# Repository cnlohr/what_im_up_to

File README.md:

# what_im_up_to
Charles: Stop putting things here, and put them in TODO.

99C99in99
 * Thinking Procedurally
 * main(...) and functions.
 * variables
 * 
 * /proc/cmdline
 * /proc/mem
 * /proc/maps

Interesting C:
 * /proc/cmdline
 * /proc/maps, /proc/exe, objdump
 
Other videos:
 * Engineering, getting from here to there.
 * James 3:3 When we put bits into the mouths of horses to make them obey us, we can turn the whole animal. 4 Or take ships as an example. Although they are so large and are driven by strong winds, they are steered by a very small rudder wherever the pilot wants to go

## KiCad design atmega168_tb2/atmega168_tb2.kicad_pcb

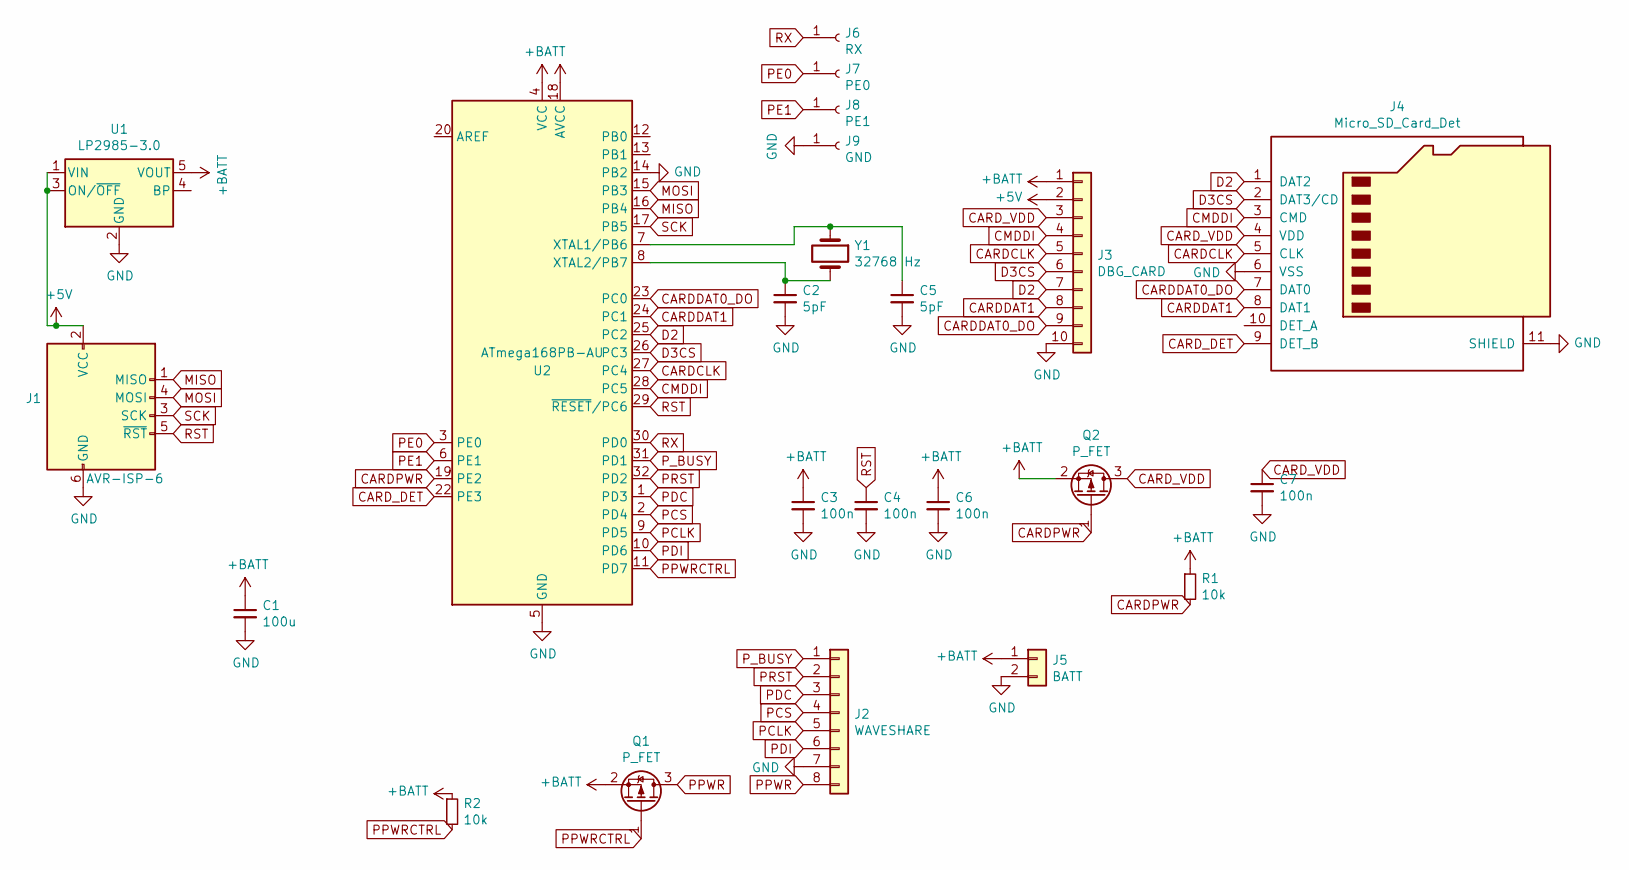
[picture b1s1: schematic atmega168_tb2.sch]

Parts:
C1: 100u; C_1206_3216Metric
C2, C5: 5pF; C_0603_1608Metric
C3, C4, C6, C7: 100n; C_0603_1608Metric
J1: AVR-ISP-6; PinHeader_2x03_P2.54mm_Vertical_SMD
J2: WAVESHARE; PinHeader_1x08_P2.54mm_Vertical_SMD_Pin1Left
J3: DBG_CARD; PinHeader_1x10_P2.54mm_Vertical_SMD_Pin1Right
J4: Micro_SD_Card_Det; MicroSD-HYC77-TF09-200
J5: BATT; PinHeader_1x02_P2.54mm_Vertical_SMD_Pin1Left
J6: RX; TestPoint_Pad_2.5x2.5mm
J7: PE0; TestPoint_Pad_2.5x2.5mm
J8: PE1; TestPoint_Pad_2.5x2.5mm
J9: GND; TestPoint_Pad_2.5x2.5mm
Q1, Q2: P_FET; SOT-23
R1, R2: 10k; R_0603_1608Metric
U1: LP2985-3.0; SOT-23-5
U2: ATmega168PB-AU; TQFP-32_7x7mm_P0.8mm
Y1: 32768 Hz; Crystal_SMD_3215-2Pin_3.2x1.5mm

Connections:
+5V: J1.2 (VCC), J3.2, U1.1 (VIN), U1.3 (ON/~OFF~)
+BATT: C1.1, C3.1, C6.1, J3.1, J5.1, Q1.2 (S), Q2.2 (S), R1.1, R2.1, U1.5 (VOUT), U2.4 (VCC), U2.18 (AVCC)
CARDCLK: J3.5, J4.5 (CLK), U2.27 (PC4)
CARDDAT0_DO: J3.9, J4.7 (DAT0), U2.23 (PC0)
CARDDAT1: J3.8, J4.8 (DAT1), U2.24 (PC1)
CARDPWR: Q2.1 (G), R1.2, U2.19 (PE2)
CARD_DET: J4.9 (DET_B), U2.22 (PE3)
CARD_VDD: C7.1, J3.3, J4.4 (VDD), Q2.3 (D)
CMDDI: J3.4, J4.3 (CMD), U2.28 (PC5)
D2: J3.7, J4.1 (DAT2), U2.25 (PC2)
D3CS: J3.6, J4.2 (DAT3/CD), U2.26 (PC3)
GND: C1.2, C2.2, C3.2, C4.2, C5.2, C6.2, C7.2, J1.6 (GND), J2.7, J3.10, J4.6 (VSS), J4.11 (SHIELD), J5.2, J9.1, U1.2 (GND), U2.5 (GND), U2.14 (PB2), U2.21 (GND)
MISO: J1.1 (MISO), U2.16 (PB4)
MOSI: J1.4 (MOSI), U2.15 (PB3)
unnamed: C2.1, U2.8 (XTAL2/PB7), Y1.2
unnamed: C5.1, U2.7 (XTAL1/PB6), Y1.1
PCLK: J2.5, U2.9 (PD5)
PCS: J2.4, U2.2 (PD4)
PDC: J2.3, U2.1 (PD3)
PDI: J2.6, U2.10 (PD6)
PE0: J7.1, U2.3 (PE0)
PE1: J8.1, U2.6 (PE1)
PPWR: J2.8, Q1.3 (D)
PPWRCTRL: Q1.1 (G), R2.2, U2.11 (PD7)
PRST: J2.2, U2.32 (PD2)
P_BUSY: J2.1, U2.31 (PD1)
RST: C4.1, J1.5 (~RST), U2.29 (~RESET~/PC6)
RX: J6.1, U2.30 (PD0)
SCK: J1.3 (SCK), U2.17 (PB5)

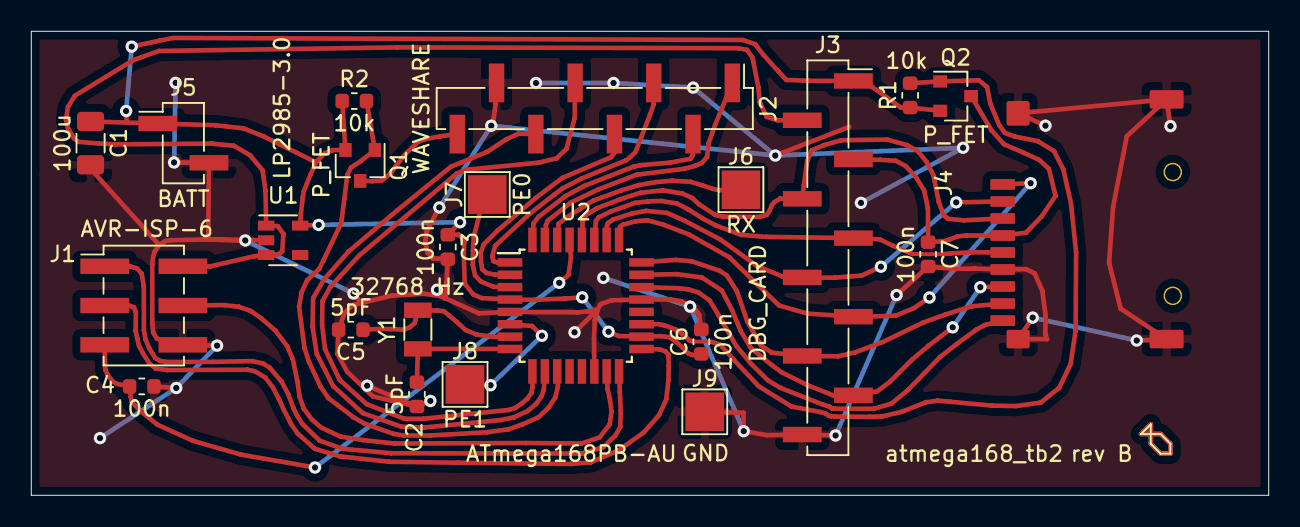
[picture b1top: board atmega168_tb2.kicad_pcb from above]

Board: 2 copper layers, 80.0 x 30.0 mm, 23 parts (0 on the bottom side), 29 nets.

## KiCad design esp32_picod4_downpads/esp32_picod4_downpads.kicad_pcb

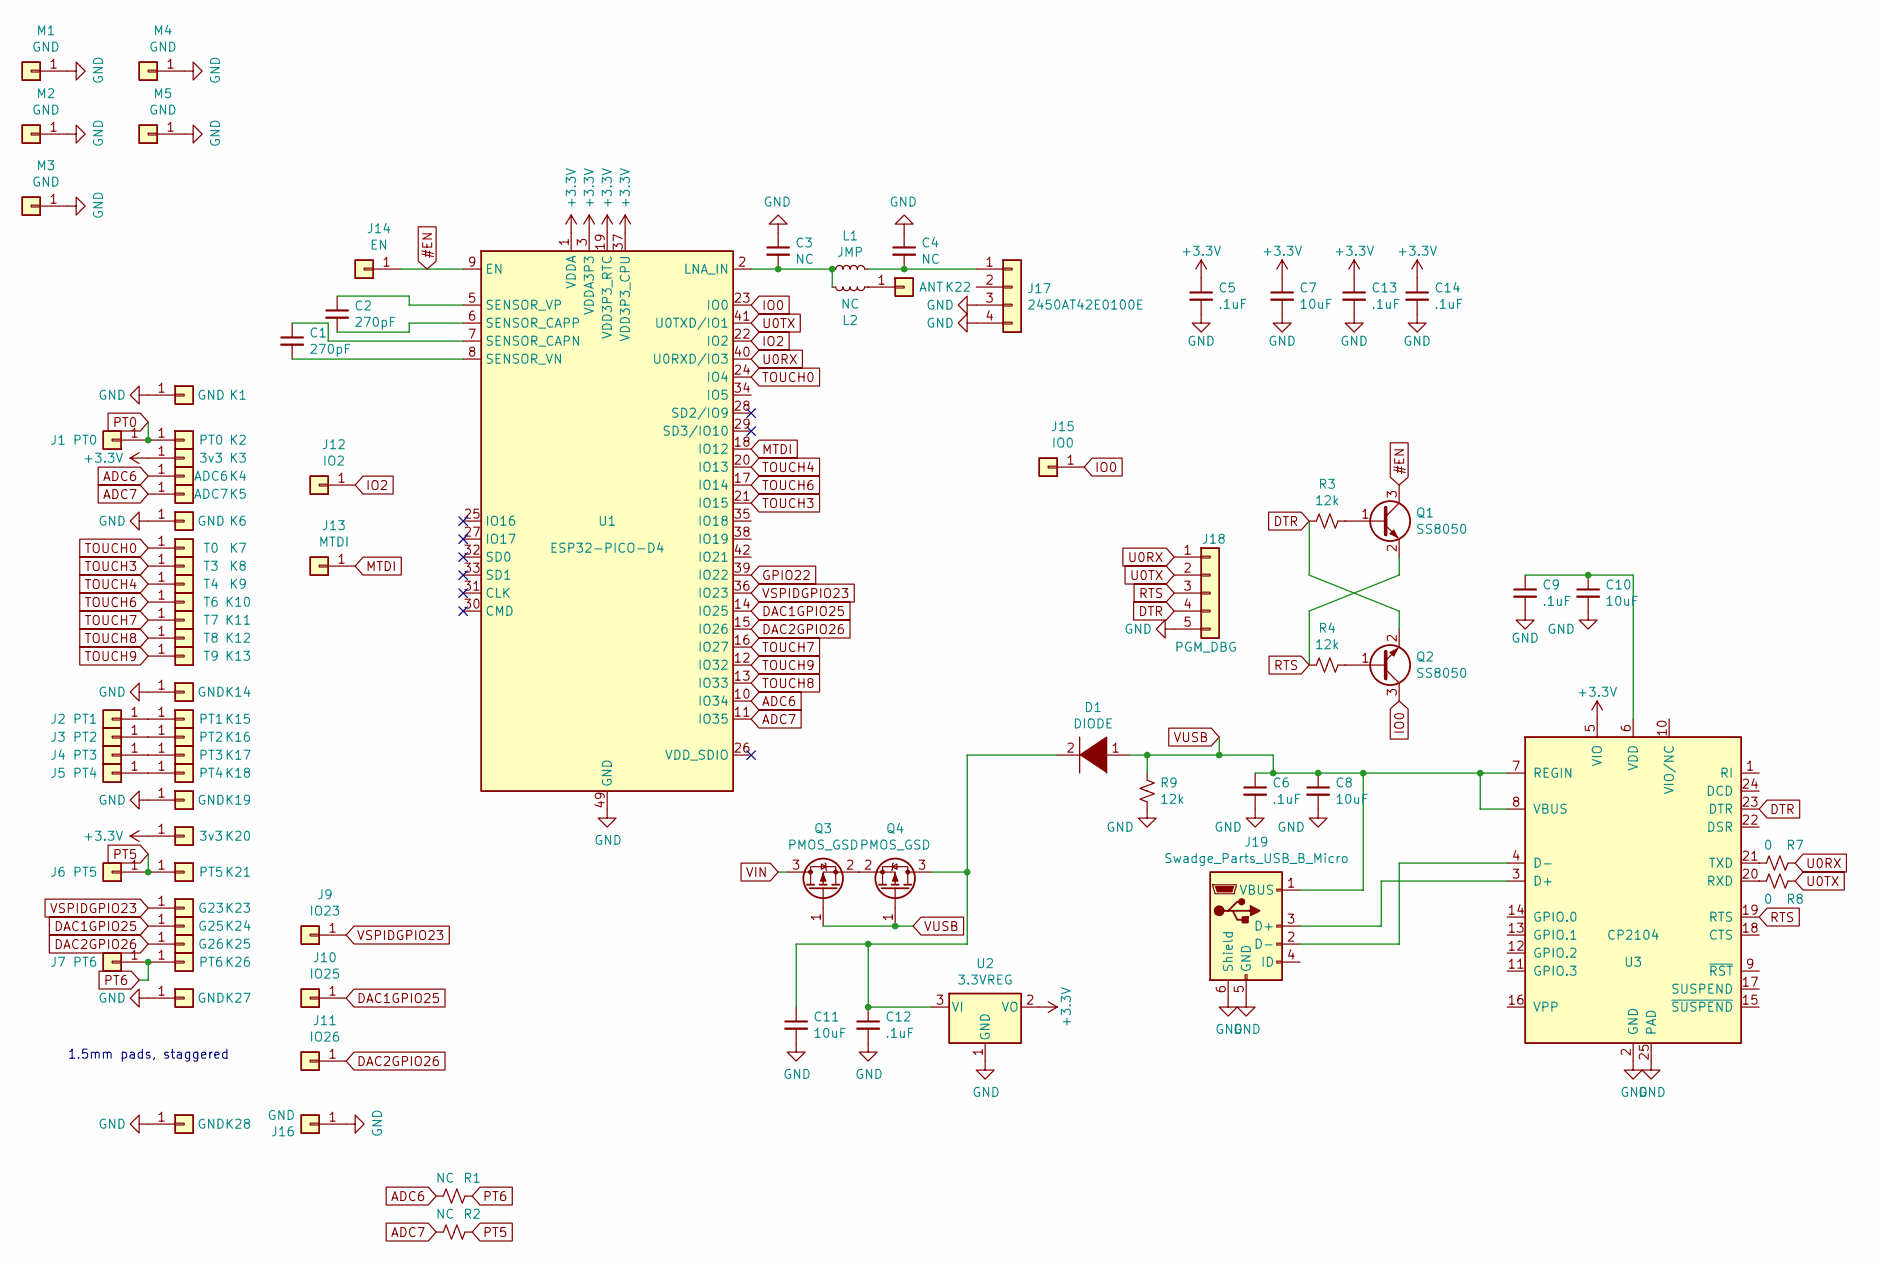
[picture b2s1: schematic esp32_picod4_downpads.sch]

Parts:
C1, C2: 270pF; C_0603_1608Metric
C3, C4: NC; C_0603_1608Metric
C5, C6, C9, C12, C13, C14: .1uF; C_0603_1608Metric
C7, C8, C10, C11: 10uF; C_0603_1608Metric
D1: DIODE; D_SOD-123
J1: PT0; TestPoint_Pad_D1.5mm
J2: PT1; TestPoint_Pad_D1.5mm
J3: PT2; TestPoint_Pad_D1.5mm
J4: PT3; TestPoint_Pad_D1.5mm
J5: PT4; TestPoint_Pad_D1.5mm
J6: PT5; TestPoint_Pad_D1.5mm
J7: PT6; TestPoint_Pad_D1.5mm
J9: IO23; TestPoint_Pad_D1.5mm
J10: IO25; TestPoint_Pad_D1.5mm
J11: IO26; TestPoint_Pad_D1.5mm
J12: IO2; TestPoint_Pad_D1.5mm
J13: MTDI; TestPoint_Pad_D1.5mm
J14: EN; TestPoint_Pad_D1.5mm
J15: IO0; TestPoint_Pad_D1.5mm
J16: GND; TestPoint_Pad_D1.5mm
J17: ‎2450AT42E0100E‎; RFANT_2450AT42E0100E
J18: PGM_DBG; PinHeader_1x05_P2.54mm_Vertical_SMD_Pin1Right
J19: Swadge_Parts_USB_B_Micro; USB_Micro-B_GCT_USB3076-30-A
K1, K6, K14, K19, K27, K28: GND; TestPoint_Pad_D1.5mm
K2: PT0; TestPoint_Pad_D1.5mm
K3, K20: 3v3; TestPoint_Pad_D1.5mm
K4: ADC6; TestPoint_Pad_D1.5mm
K5: ADC7; TestPoint_Pad_D1.5mm
K7: T0; TestPoint_Pad_D1.5mm
K8: T3; TestPoint_Pad_D1.5mm
K9: T4; TestPoint_Pad_D1.5mm
K10: T6; TestPoint_Pad_D1.5mm
K11: T7; TestPoint_Pad_D1.5mm
K12: T8; TestPoint_Pad_D1.5mm
K13: T9; TestPoint_Pad_D1.5mm
K15: PT1; TestPoint_Pad_D1.5mm
K16: PT2; TestPoint_Pad_D1.5mm
K17: PT3; TestPoint_Pad_D1.5mm
K18: PT4; TestPoint_Pad_D1.5mm
K21: PT5; TestPoint_Pad_D1.5mm
K22: ANT; TestPoint_Pad_D1.5mm
K23: G23; TestPoint_Pad_D1.5mm
K24: G25; TestPoint_Pad_D1.5mm
K25: G26; TestPoint_Pad_D1.5mm
K26: PT6; TestPoint_Pad_D1.5mm
L1: JMP; L_0603_1608Metric
L2: NC; L_0603_1608Metric
M1, M2, M3, M4, M5: GND; MountingHole_3.2mm_M3_Pad_Via
Q1, Q2: SS8050; SOT-23
Q3, Q4: PMOS_GSD; SOT-23
R1, R2: NC; R_0603_1608Metric
R3, R4, R9: 12k; R_0603_1608Metric
R7, R8: 0; R_0603_1608Metric
U1: ESP32-PICO-D4; QFN-48-1EP_7x7mm_P0.5mm_EP5.3x5.3mm
U2: 3.3VREG; SOT-23
U3: CP2104; QFN-24-1EP_4x4mm_P0.5mm_EP2.6x2.6mm

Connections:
#EN: J14.1, Q1.3 (C), U1.9 (EN)
+3V3: C5.1, C7.1, C13.1, C14.1, K3.1, K20.1, U1.1 (VDDA), U1.3 (VDDA3P3), U1.4 (VDDA3P3), U1.19 (VDD3P3_RTC), U1.37 (VDD3P3_CPU), U1.43 (VDDA), U1.46 (VDDA), U2.2 (VO), U3.5 (VIO)
ADC6: K4.1, R1.2, U1.10 (IO34)
ADC7: K5.1, R2.2, U1.11 (IO35)
DAC1GPIO25: J10.1, K24.1, U1.14 (IO25)
DAC2GPIO26: J11.1, K25.1, U1.15 (IO26)
DTR: J18.4, Q2.2 (E), R3.2, U3.23 (DTR)
GND: C3.1, C4.1, C5.2, C6.2, C7.2, C8.2, C9.2, C10.2, C11.2, C12.2, C13.2, C14.2, J16.1, J17.3, J17.4, J18.5, J19.5 (GND), J19.6 (Shield), K1.1, K6.1, K14.1, K19.1, K27.1, K28.1, M1.1, M2.1, M3.1, M4.1, M5.1, R9.2, U1.49 (GND), U2.1 (GND), U3.2 (GND), U3.25 (PAD)
GPIO22: U1.39 (IO22)
IO0: J15.1, Q2.3 (C), U1.23 (IO0)
IO2: J12.1, U1.22 (IO2)
MTDI: J13.1, U1.18 (IO12)
unnamed: C1.1, U1.7 (SENSOR_CAPN)
unnamed: C1.2, U1.8 (SENSOR_VN)
unnamed: C2.1, U1.5 (SENSOR_VP)
unnamed: C2.2, U1.6 (SENSOR_CAPP)
unnamed: C3.2, L1.1, L2.2, U1.2 (LNA_IN)
unnamed: C4.2, J17.1, L1.2
unnamed: C9.1, C10.1, U3.6 (VDD)
unnamed: C11.1, C12.1, D1.2 (A), Q4.3 (D), U2.3 (VI)
unnamed: J2.1, K15.1
unnamed: J3.1, K16.1
unnamed: J4.1, K17.1
unnamed: J5.1, K18.1
unnamed: J19.2 (D-), U3.4 (D-)
unnamed: J19.3 (D+), U3.3 (D+)
unnamed: K22.1, L2.1
unnamed: Q1.1 (B), R3.1
unnamed: Q2.1 (B), R4.1
unnamed: Q3.2 (S), Q4.2 (S)
unnamed: R7.2, U3.21 (TXD)
unnamed: R8.1, U3.20 (RXD)
PT0: J1.1, K2.1
PT5: J6.1, K21.1, R2.1
PT6: J7.1, K26.1, R1.1
RTS: J18.3, Q1.2 (E), R4.2, U3.19 (RTS)
TOUCH0: K7.1, U1.24 (IO4)
TOUCH3: K8.1, U1.21 (IO15)
TOUCH4: K9.1, U1.20 (IO13)
TOUCH6: K10.1, U1.17 (IO14)
TOUCH7: K11.1, U1.16 (IO27)
TOUCH8: K12.1, U1.13 (IO33)
TOUCH9: K13.1, U1.12 (IO32)
U0RX: J18.1, R7.1, U1.40 (U0RXD/IO3)
U0TX: J18.2, R8.2, U1.41 (U0TXD/IO1)
VIN: Q3.3 (D)
VSPIDGPIO23: J9.1, K23.1, U1.36 (IO23)
VUSB: C6.1, C8.1, D1.1 (K), J19.1 (VBUS), Q3.1 (G), Q4.1 (G), R9.1, U3.7 (REGIN), U3.8 (VBUS)

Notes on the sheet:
1.5mm pads, staggered

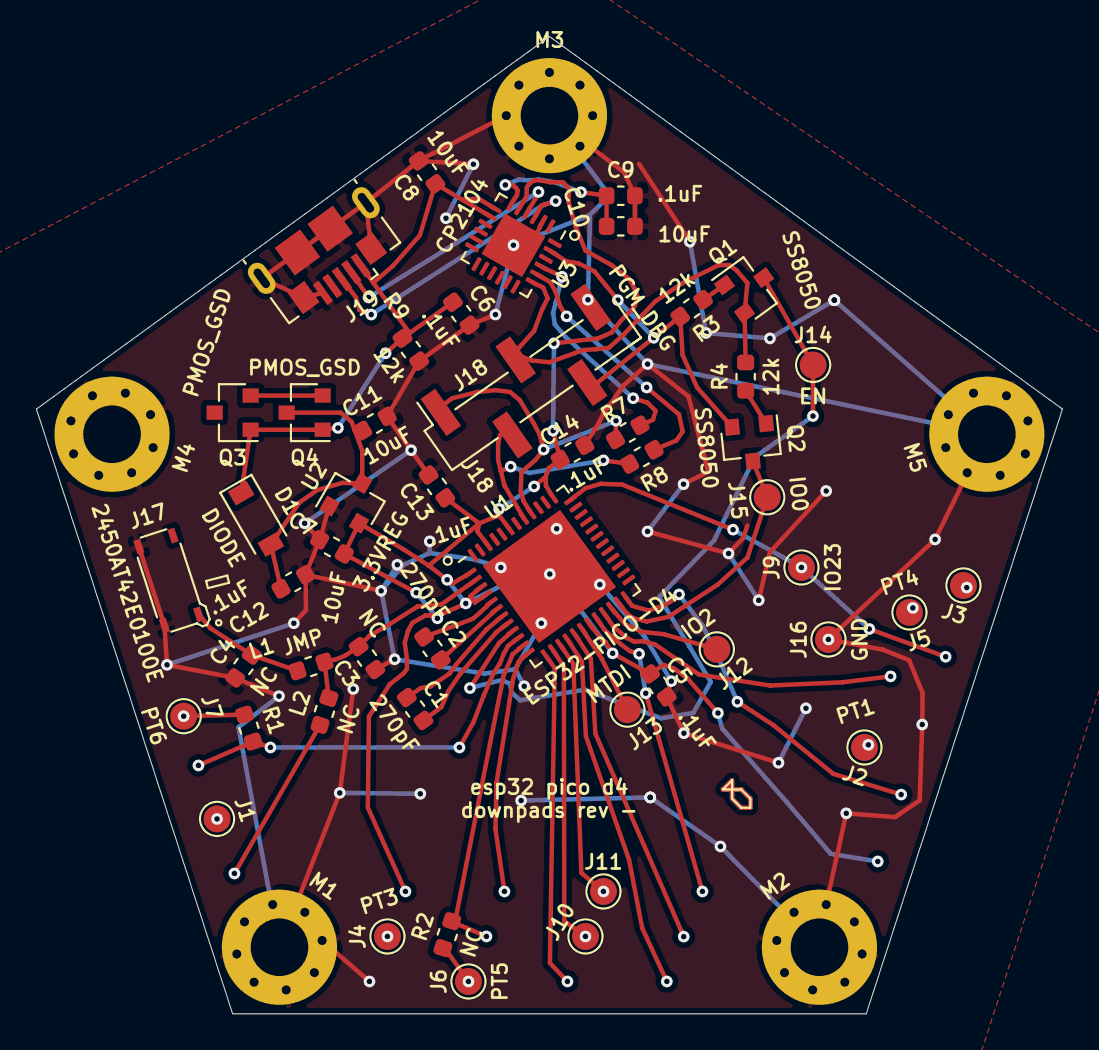
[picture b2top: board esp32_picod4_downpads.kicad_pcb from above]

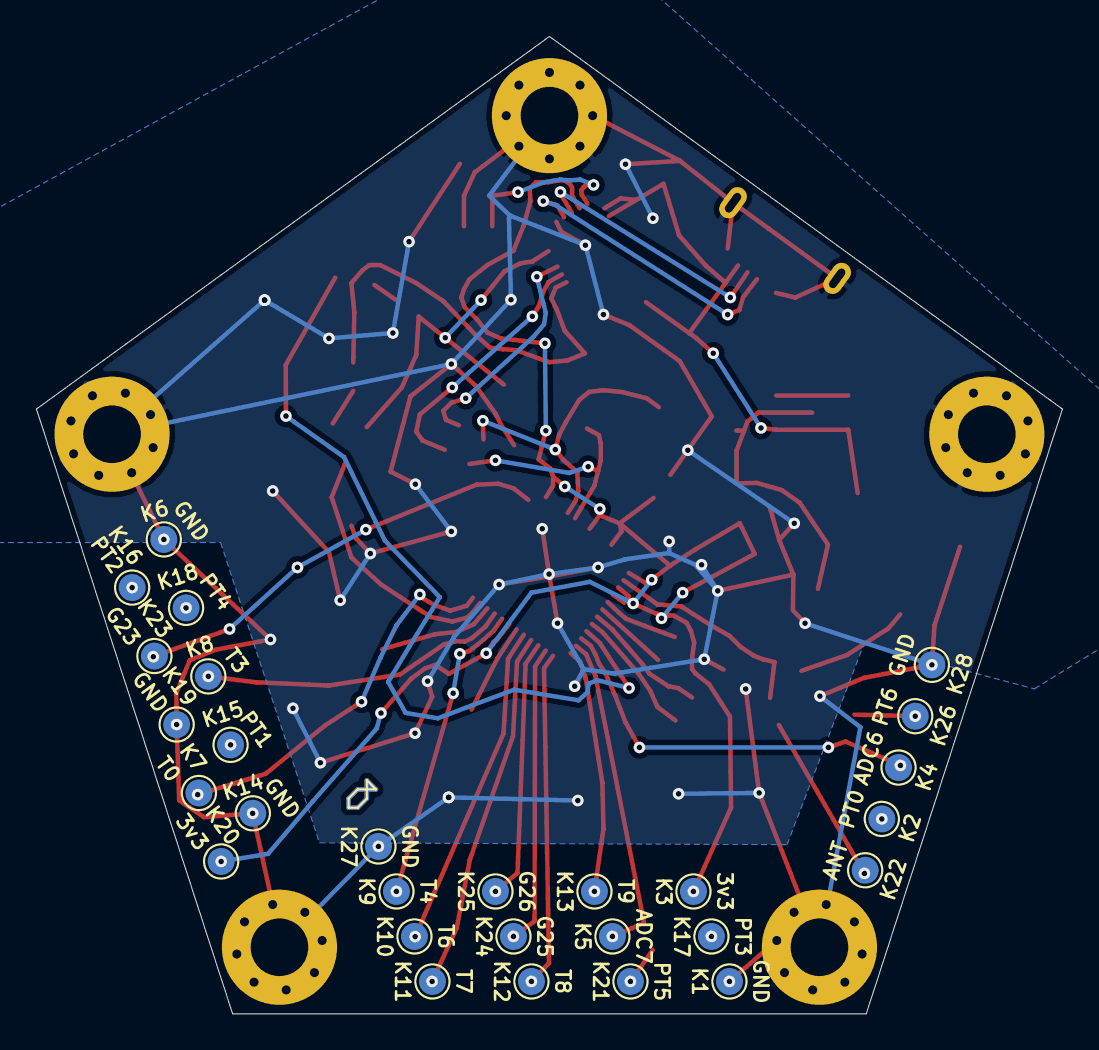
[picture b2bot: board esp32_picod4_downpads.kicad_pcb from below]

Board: 2 copper layers, 57.0 x 54.3 mm, 82 parts (28 on the bottom side), 46 nets.

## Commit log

2018-05-02 update random notes
2018-05-03 Add notes about installing armbian
2018-05-03 bump instructions
2018-05-03 Add course file
2018-05-04 bumpt instructions
2018-05-04 Add notes about trying to install libmali
2018-05-20 Getting Linux running on a Powerspect 1510
    I've taken some notes about what I needed to do to get Linux running on my powerspec. Most notably, with regards to the NVIDIA + Intel card. This is the same laptop that's built on a clevo frame with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
    I admit some of this is a little hocus pocus and may not be needed, but I do currently have a working system.
    In BIOS, set the video card to Dedicated. It's very difficult to get the system installed if you're dealing with the whole hybrid thing.
    You can then install your system, and install the NVIDIA drivers.
    Once you're booted into your new system on NVIDIA, you can edit your grub defaults. ```/etc
2020-07-28 bump files
2020-07-28 Bump
2020-07-29 Forgot to upload design
2020-08-07 Add some libraries.
2020-08-08 Starting down another path for mom's epaper gift.
2020-08-08 bump.
2020-08-09 Complete thing for mom's picture frame.
2020-08-09 Add rescue lib.
2020-08-20 Move out downpads
2020-09-15 update USB connector
2020-10-26 Remove mom's epaper thing - it's moved over here: https://github.com/cnlohr/epaper_projects/tree/master/atmega168pb_waveshare_color
2020-11-20 Start with an initial draft.
